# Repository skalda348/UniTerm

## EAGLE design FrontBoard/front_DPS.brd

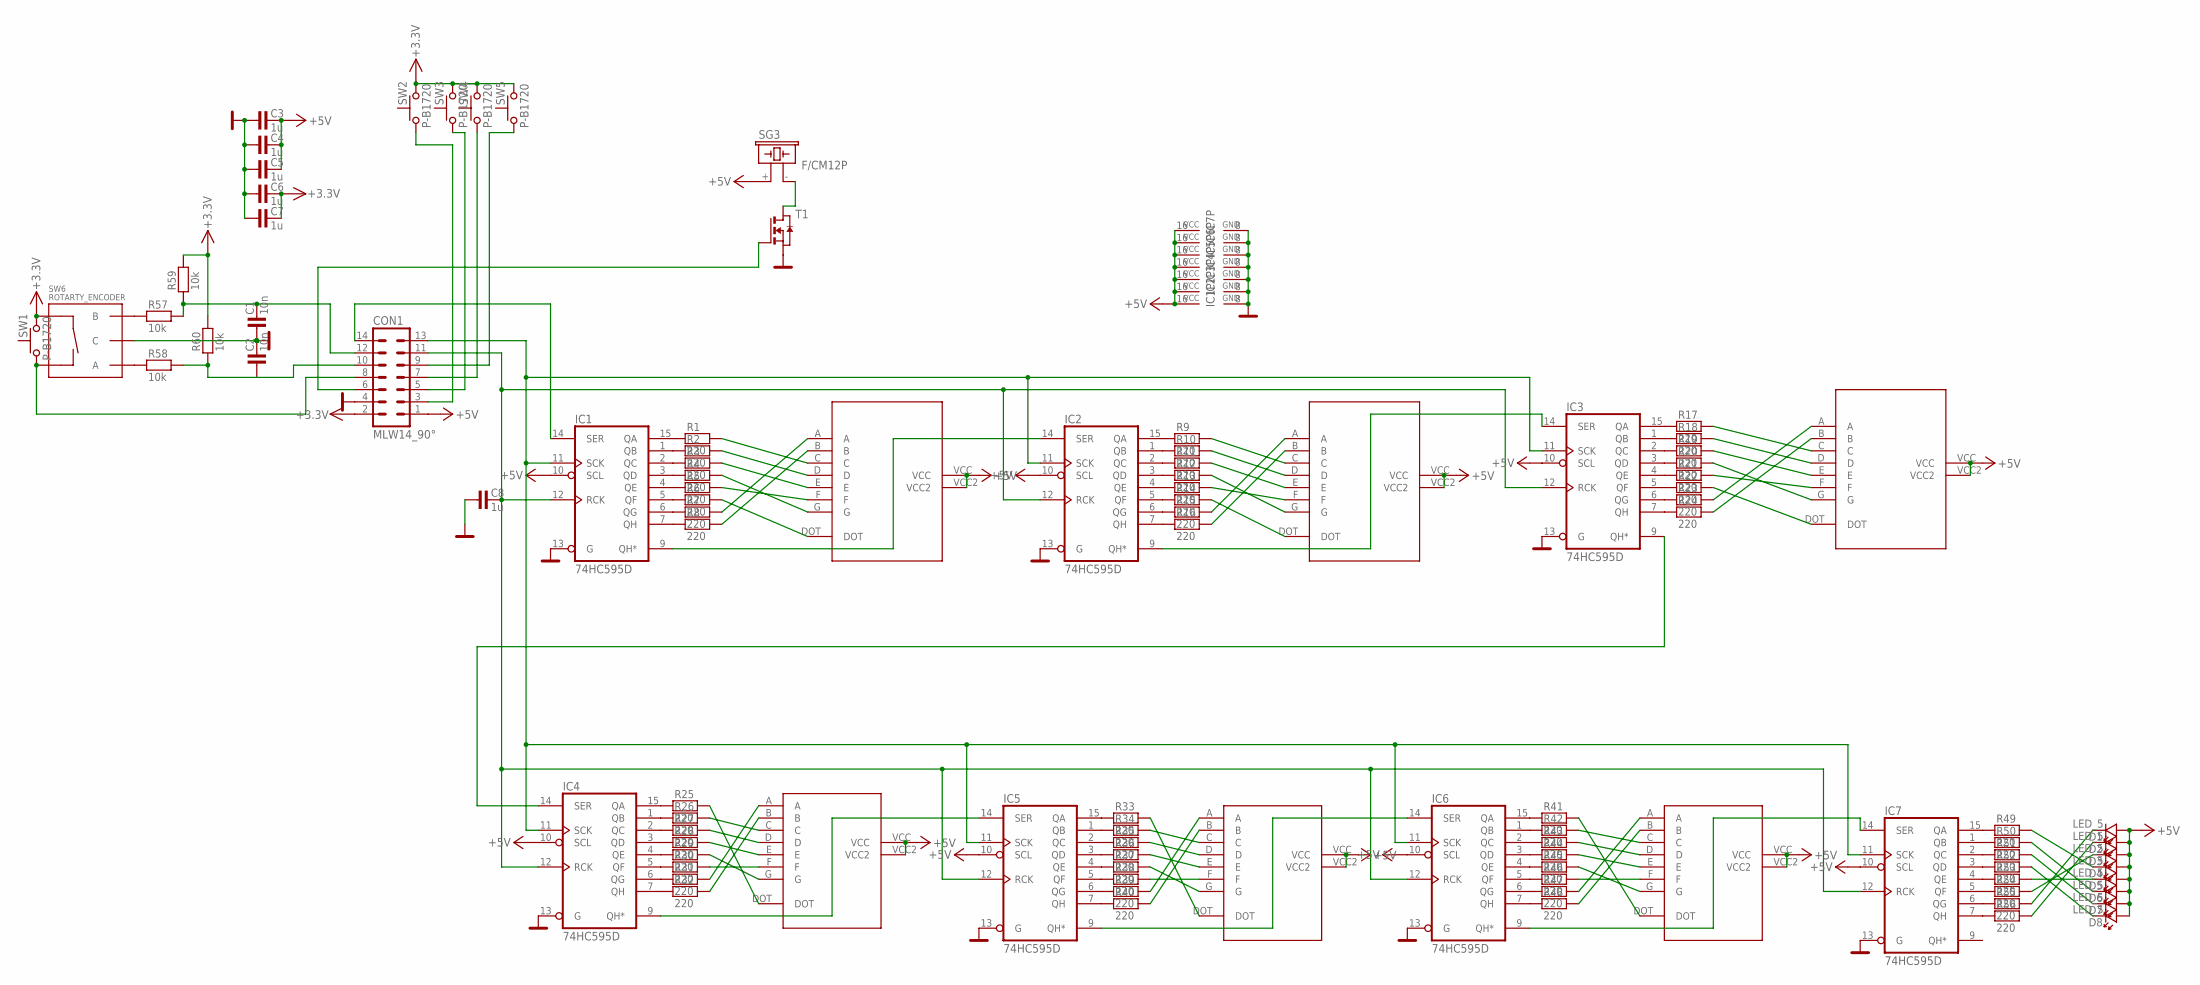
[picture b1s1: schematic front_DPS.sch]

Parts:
C1, C2: 10n; 1206
C3, C4, C5, C6, C7, C8: 1u; 1206
CON1: MLW14_90°; MLW14A
D1, D2, D3, D4, D5, D6, D7, D8: LED_5
IC1, IC2, IC3, IC4, IC5, IC6, IC7: 74HC595D; SO16
R1, R2, R3, R4, R5, R6, R7, R8, R9, R10, R11, R12, R13, R14, R15, R16, R17, R18, R19, R20, R21, R22, R23, R24, R25, R26, R27, R28, R29, R30, R31, R32, R33, R34, R35, R36, R37, R38, R39, R40, R41, R42, R43, R44, R45, R46, R47, R48, R49, R50, R51, R52, R53, R54, R55, R56: 220; 1206
R57, R58, R59, R60: 10k; 1206
SG3: F/CM12P
SW1, SW2, SW3, SW4, SW5: P-B1720
SW6: ROTARTY_ENCODER; ROTARY_ENC_PLAIN
T1: NMOSSOT223; SOT223
U$1, U$2, U$3: 7-SEGMENT-24X34-ANODE; 7-SEGMENT-24X34
U$4, U$5, U$6: 7-SEGMENT-44X30-ANODE; 7-SEGMENT-44X30

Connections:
+5V: C3.2, C4.2, C5.2, CON1.1, D1.A, D2.A, D3.A, D4.A, D5.A, D6.A, D7.A, D8.A, IC1.10 (SCL), IC1.16 (VCC), IC2.10 (SCL), IC2.16 (VCC), IC3.10 (SCL), IC3.16 (VCC), IC4.10 (SCL), IC4.16 (VCC), IC5.10 (SCL), IC5.16 (VCC), IC6.10 (SCL), IC6.16 (VCC), IC7.10 (SCL), IC7.16 (VCC), SG3.+ (1), U$1.VCC, U$1.VCC2, U$2.VCC, U$2.VCC2, U$3.VCC, U$3.VCC2, U$4.VCC, U$4.VCC2, U$5.VCC, U$5.VCC2, U$6.VCC, U$6.VCC2
GND: C1.1, C2.2, C3.1, C4.1, C5.1, C6.1, C7.1, C8.1, CON1.4, IC1.8 (GND), IC1.13 (G), IC2.8 (GND), IC2.13 (G), IC3.8 (GND), IC3.13 (G), IC4.8 (GND), IC4.13 (G), IC5.8 (GND), IC5.13 (G), IC6.8 (GND), IC6.13 (G), IC7.8 (GND), IC7.13 (G), SW6.C, T1.3 (S)
unnamed: IC1.15 (QA), R1.1
unnamed: IC1.1 (QB), R2.1
unnamed: IC1.2 (QC), R3.1
unnamed: IC1.3 (QD), R4.1
unnamed: IC1.4 (QE), R5.1
unnamed: IC1.5 (QF), R6.1
unnamed: IC1.6 (QG), R7.1
unnamed: IC1.7 (QH), R8.1
unnamed: R1.2, U$4.C
unnamed: R4.2, U$4.G
unnamed: R5.2, U$4.F
unnamed: R6.2, U$4.DOT
unnamed: R7.2, U$4.A
unnamed: R8.2, U$4.B
unnamed: R2.2, U$4.D
unnamed: IC2.15 (QA), R9.1
unnamed: IC2.1 (QB), R10.1
unnamed: IC2.2 (QC), R11.1
unnamed: IC2.3 (QD), R12.1
unnamed: IC2.4 (QE), R13.1
unnamed: IC2.5 (QF), R14.1
unnamed: IC3.7 (QH), R24.1
unnamed: R15.2, U$5.A
unnamed: IC2.6 (QG), R15.1
unnamed: IC1.9 (QH*), IC2.14 (SER)
unnamed: IC2.9 (QH*), IC3.14 (SER)
unnamed: IC2.7 (QH), R16.1
unnamed: IC7.15 (QA), R49.1
unnamed: IC7.1 (QB), R50.1
unnamed: IC7.2 (QC), R51.1
unnamed: IC7.3 (QD), R52.1
unnamed: IC7.4 (QE), R53.1
unnamed: IC7.5 (QF), R54.1
unnamed: IC7.6 (QG), R55.1
unnamed: IC7.7 (QH), R56.1
unnamed: D6.K, R50.2
unnamed: D4.K, R49.2
unnamed: D7.K, R51.2
unnamed: D8.K, R52.2
unnamed: D5.K, R53.2
unnamed: D3.K, R54.2
unnamed: D1.K, R55.2
unnamed: D2.K, R56.2
unnamed: R16.2, U$5.B
unnamed: R9.2, U$5.C
unnamed: IC3.9 (QH*), IC4.14 (SER)
unnamed: IC5.15 (QA), R33.1
unnamed: IC5.1 (QB), R34.1
unnamed: IC5.2 (QC), R35.1
unnamed: IC4.9 (QH*), IC5.14 (SER)
unnamed: IC5.3 (QD), R36.1
unnamed: IC5.9 (QH*), IC6.14 (SER)
unnamed: IC5.4 (QE), R37.1
unnamed: IC6.9 (QH*), IC7.14 (SER)
unnamed: IC5.5 (QF), R38.1
unnamed: IC5.6 (QG), R39.1
unnamed: IC5.7 (QH), R40.1
unnamed: R39.2, U$2.A
unnamed: R40.2, U$2.B
unnamed: R33.2, U$2.DOT
unnamed: R34.2, U$2.C
unnamed: R35.2, U$2.D
unnamed: CON1.13, IC1.11 (SCK), IC2.11 (SCK), IC3.11 (SCK), IC4.11 (SCK), IC5.11 (SCK), IC6.11 (SCK), IC7.11 (SCK)
unnamed: SG3.- (2), T1.2 (D), T1.4 (D)
unnamed: C1.2, CON1.12, R57.2, R59.1
unnamed: C8.2, CON1.11, IC1.12 (RCK), IC2.12 (RCK), IC3.12 (RCK), IC4.12 (RCK), IC5.12 (RCK), IC6.12 (RCK), IC7.12 (RCK)
unnamed: R36.2, U$2.E
unnamed: R38.2, U$2.F
unnamed: IC4.15 (QA), R25.1
unnamed: IC4.1 (QB), R26.1
unnamed: IC4.2 (QC), R27.1
unnamed: IC4.3 (QD), R28.1
unnamed: IC4.4 (QE), R29.1
unnamed: IC4.5 (QF), R30.1
unnamed: IC4.6 (QG), R31.1
unnamed: IC4.7 (QH), R32.1
unnamed: R25.2, U$1.DOT
unnamed: R26.2, U$1.C
unnamed: R27.2, U$1.D
unnamed: R28.2, U$1.E
unnamed: R29.2, U$1.G
unnamed: R30.2, U$1.F
unnamed: R31.2, U$1.A
unnamed: IC6.15 (QA), R41.1
unnamed: IC6.1 (QB), R42.1
unnamed: IC6.2 (QC), R43.1
unnamed: IC6.3 (QD), R44.1
unnamed: IC6.4 (QE), R45.1
unnamed: IC6.5 (QF), R46.1
unnamed: IC6.6 (QG), R47.1
unnamed: IC6.7 (QH), R48.1
unnamed: R41.2, U$3.DOT
unnamed: R47.2, U$3.A
unnamed: R48.2, U$3.B
unnamed: R42.2, U$3.C
unnamed: R43.2, U$3.D
unnamed: R44.2, U$3.E
unnamed: R46.2, U$3.F
unnamed: R10.2, U$5.D
unnamed: R11.2, U$5.E
unnamed: R13.2, U$5.F
unnamed: R12.2, U$5.G
unnamed: R14.2, U$5.DOT
unnamed: IC3.15 (QA), R17.1
unnamed: IC3.1 (QB), R18.1
unnamed: IC3.2 (QC), R19.1
unnamed: IC3.3 (QD), R20.1
unnamed: IC3.4 (QE), R21.1
unnamed: IC3.5 (QF), R22.1
unnamed: IC3.6 (QG), R23.1
unnamed: R23.2, U$6.A
unnamed: R24.2, U$6.B
unnamed: R17.2, U$6.C
unnamed: R18.2, U$6.D
unnamed: R19.2, U$6.E
unnamed: R20.2, U$6.G
unnamed: R21.2, U$6.F
unnamed: R22.2, U$6.DOT
unnamed: R3.2, U$4.E
unnamed: R32.2, U$1.B
unnamed: R37.2, U$2.G
unnamed: R45.2, U$3.G
unnamed: CON1.14, IC1.14 (SER)
unnamed: CON1.9, SW5.1
unnamed: CON1.7, SW4.1
unnamed: CON1.5, SW3.1
unnamed: C2.1, CON1.10, R58.2, R60.1
unnamed: CON1.6, T1.1 (G)
unnamed: R57.1, SW6.B
unnamed: CON1.3, SW2.1
unnamed: CON1.8, SW1.1, SW6.SW-
unnamed: R58.1, SW6.A
VCC: C6.2, C7.2, CON1.2, R59.2, R60.2, SW1.2, SW2.2, SW3.2, SW4.2, SW5.2, SW6.SW+

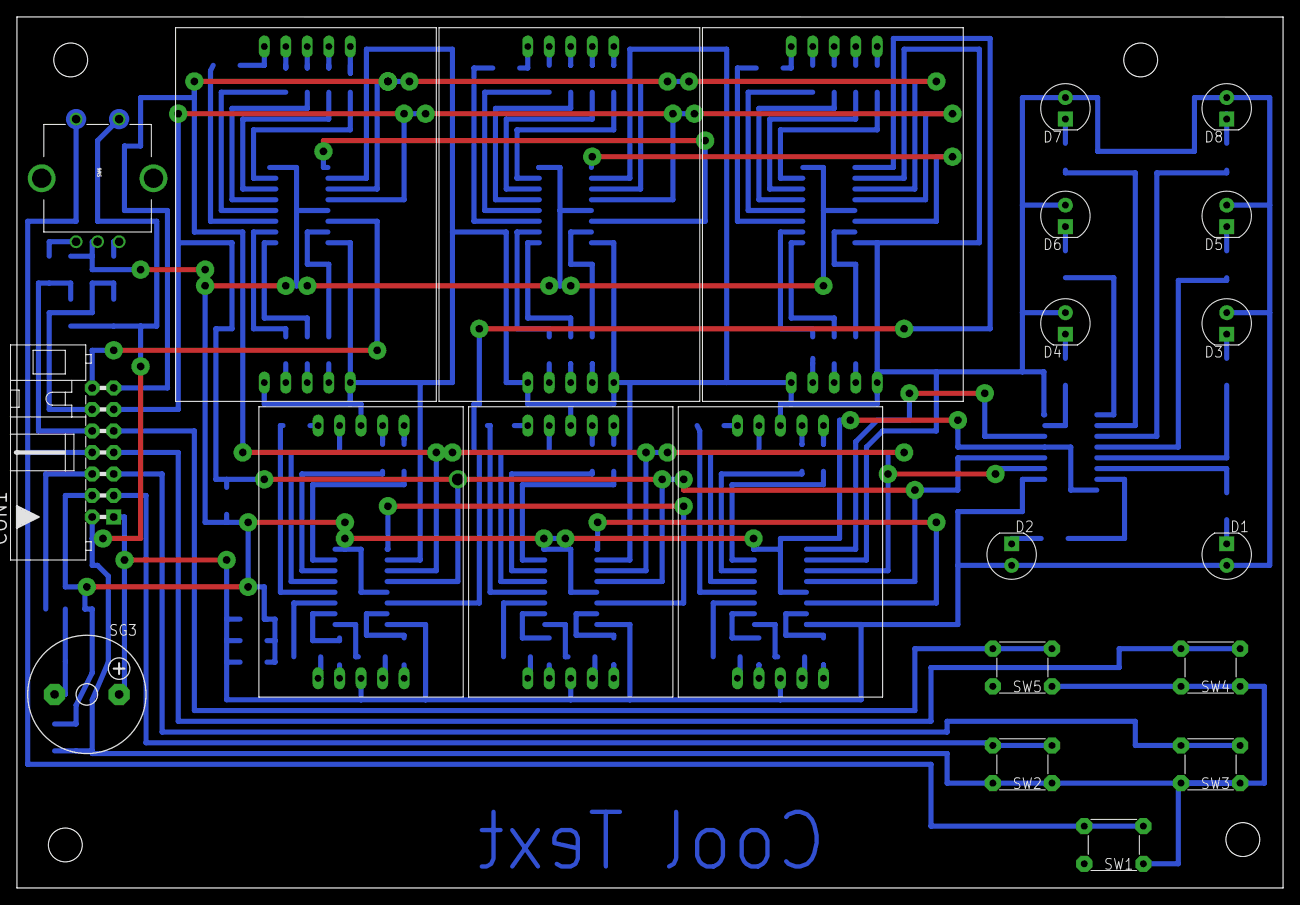
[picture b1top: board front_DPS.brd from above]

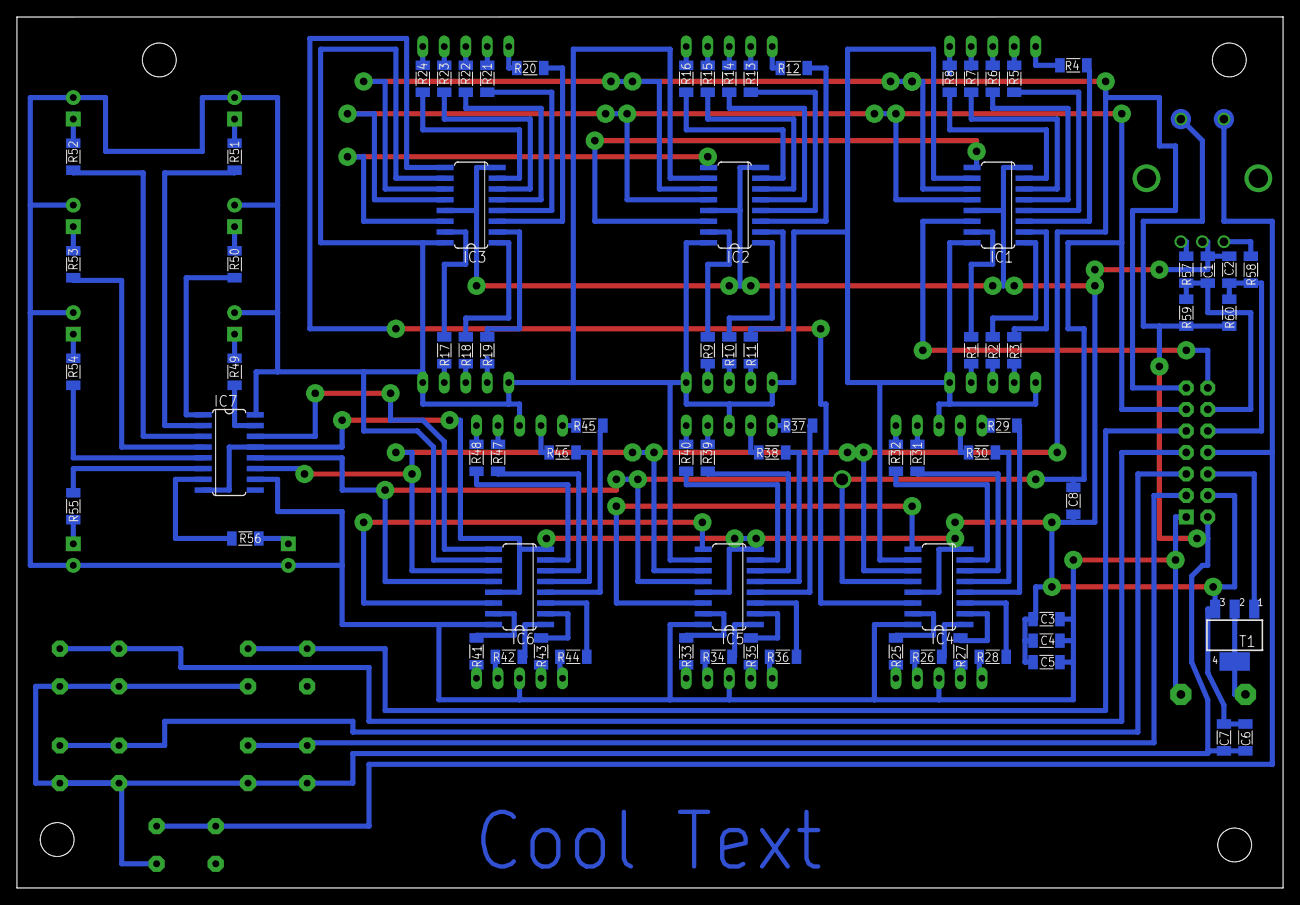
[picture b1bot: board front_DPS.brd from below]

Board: 2 copper layers, 149.5 x 102.9 mm, 98 parts (76 on the bottom side), 135 nets.

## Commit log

2014-08-13 Add MainBoard schematic with MCU and SWD interface
2014-08-13 Initial FrontBoard
2014-08-13 Initial SenzorBoard
2014-09-09 Add power switch schematic
2014-11-18 Added conectors for: nRF and Front board

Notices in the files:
parts and their libraries:
Copyright (C) PaJa 2001-2011
Copyright (C) PaJa 2011
SparkFun-Electromechanical: Licensing: Creative Commons ShareAlike 4.0 International - https://creativecommons.org/licenses/by-sa/4.0
